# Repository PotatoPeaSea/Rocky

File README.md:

# Rocky — pentapod walker

Five-legged walking robot inspired by Rocky (Project Hail Mary).

- `fusion/` — Fusion 360 build scripts and BOM
- `pcb/` — integrated control PCB (KiCad): schematic, layout, STEP, fab outputs
- `sim/` — MuJoCo model and RL training environment
- `docs/` — design notes

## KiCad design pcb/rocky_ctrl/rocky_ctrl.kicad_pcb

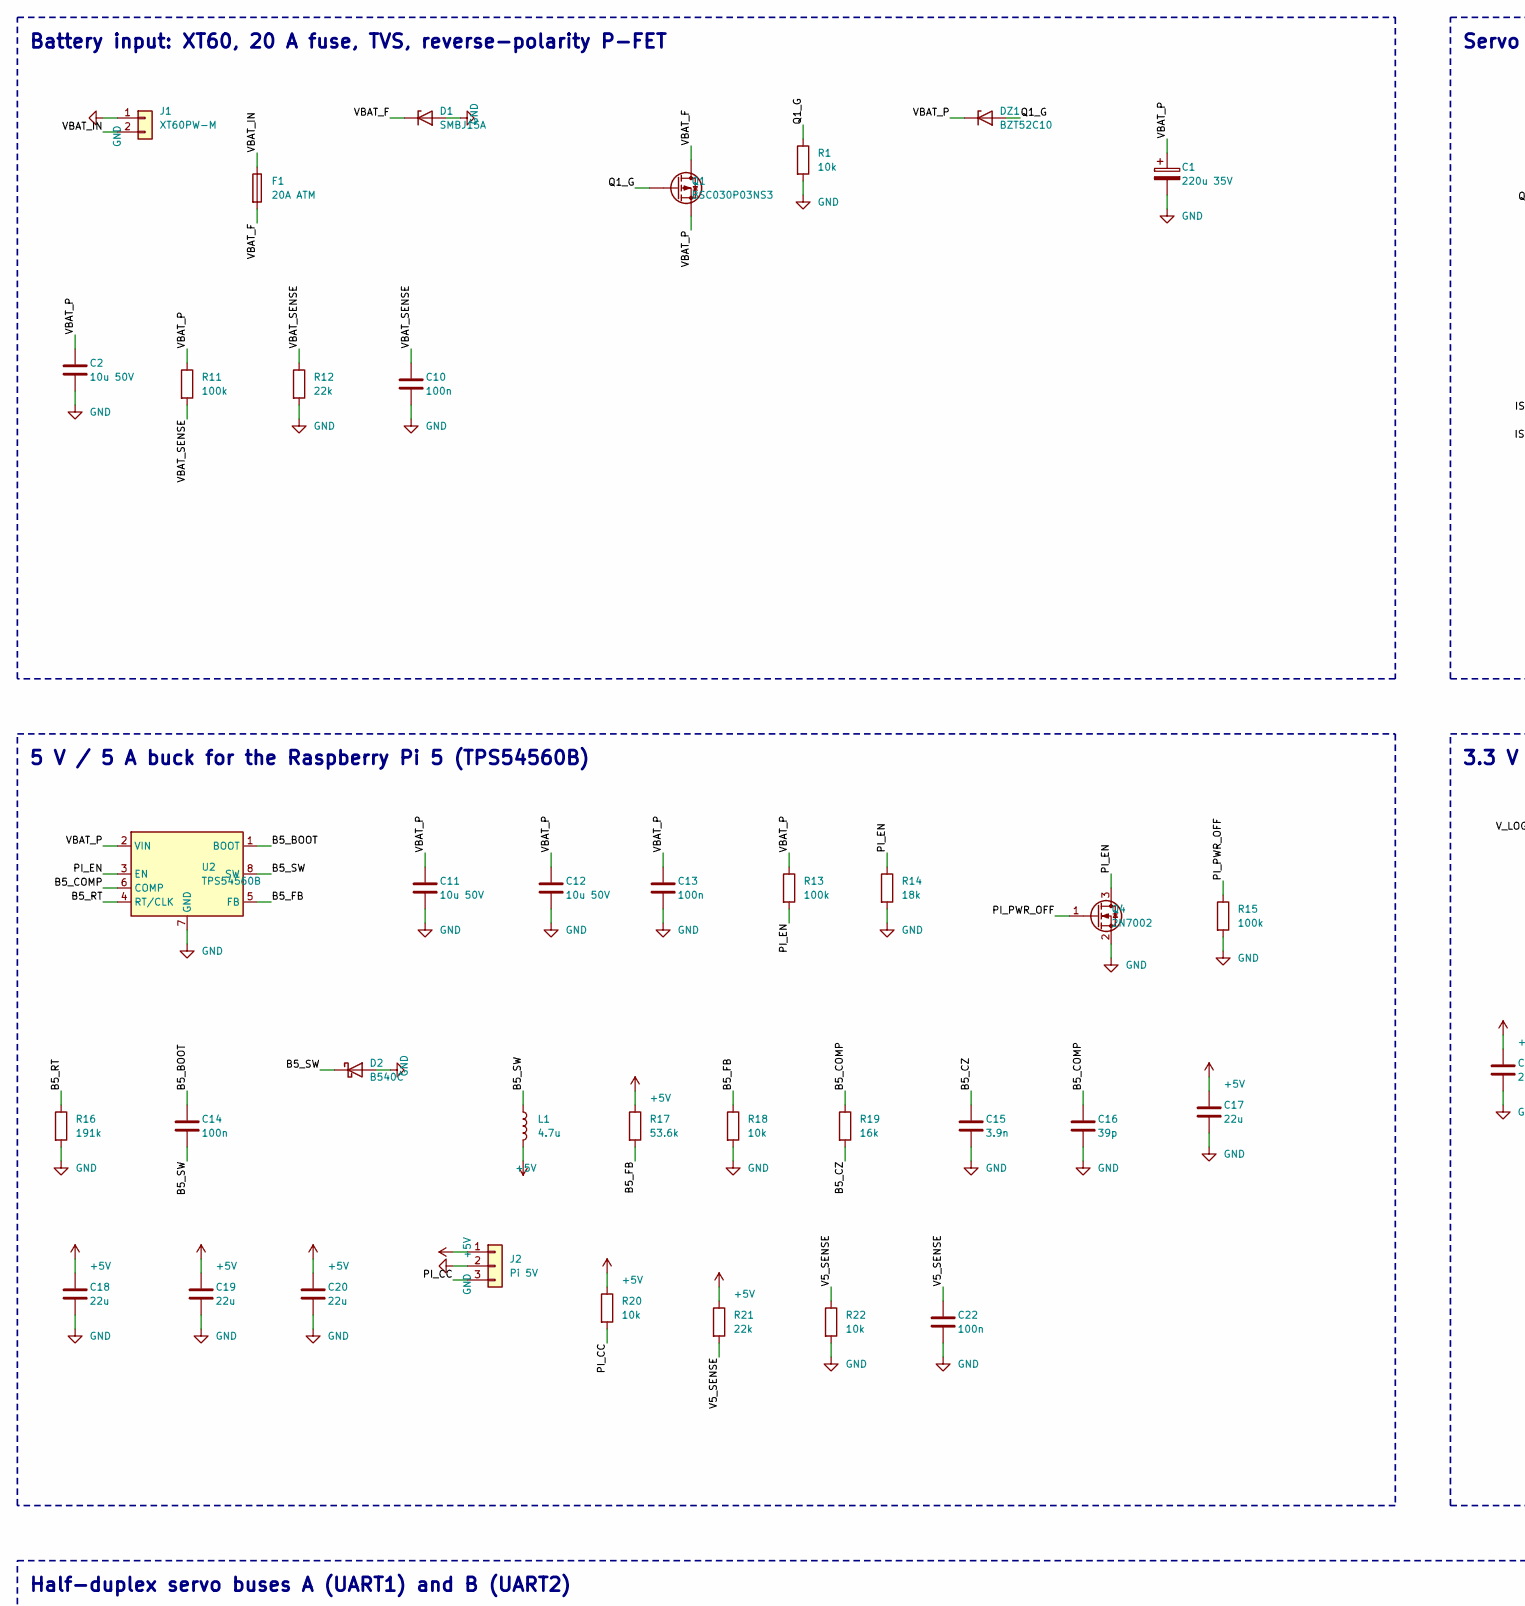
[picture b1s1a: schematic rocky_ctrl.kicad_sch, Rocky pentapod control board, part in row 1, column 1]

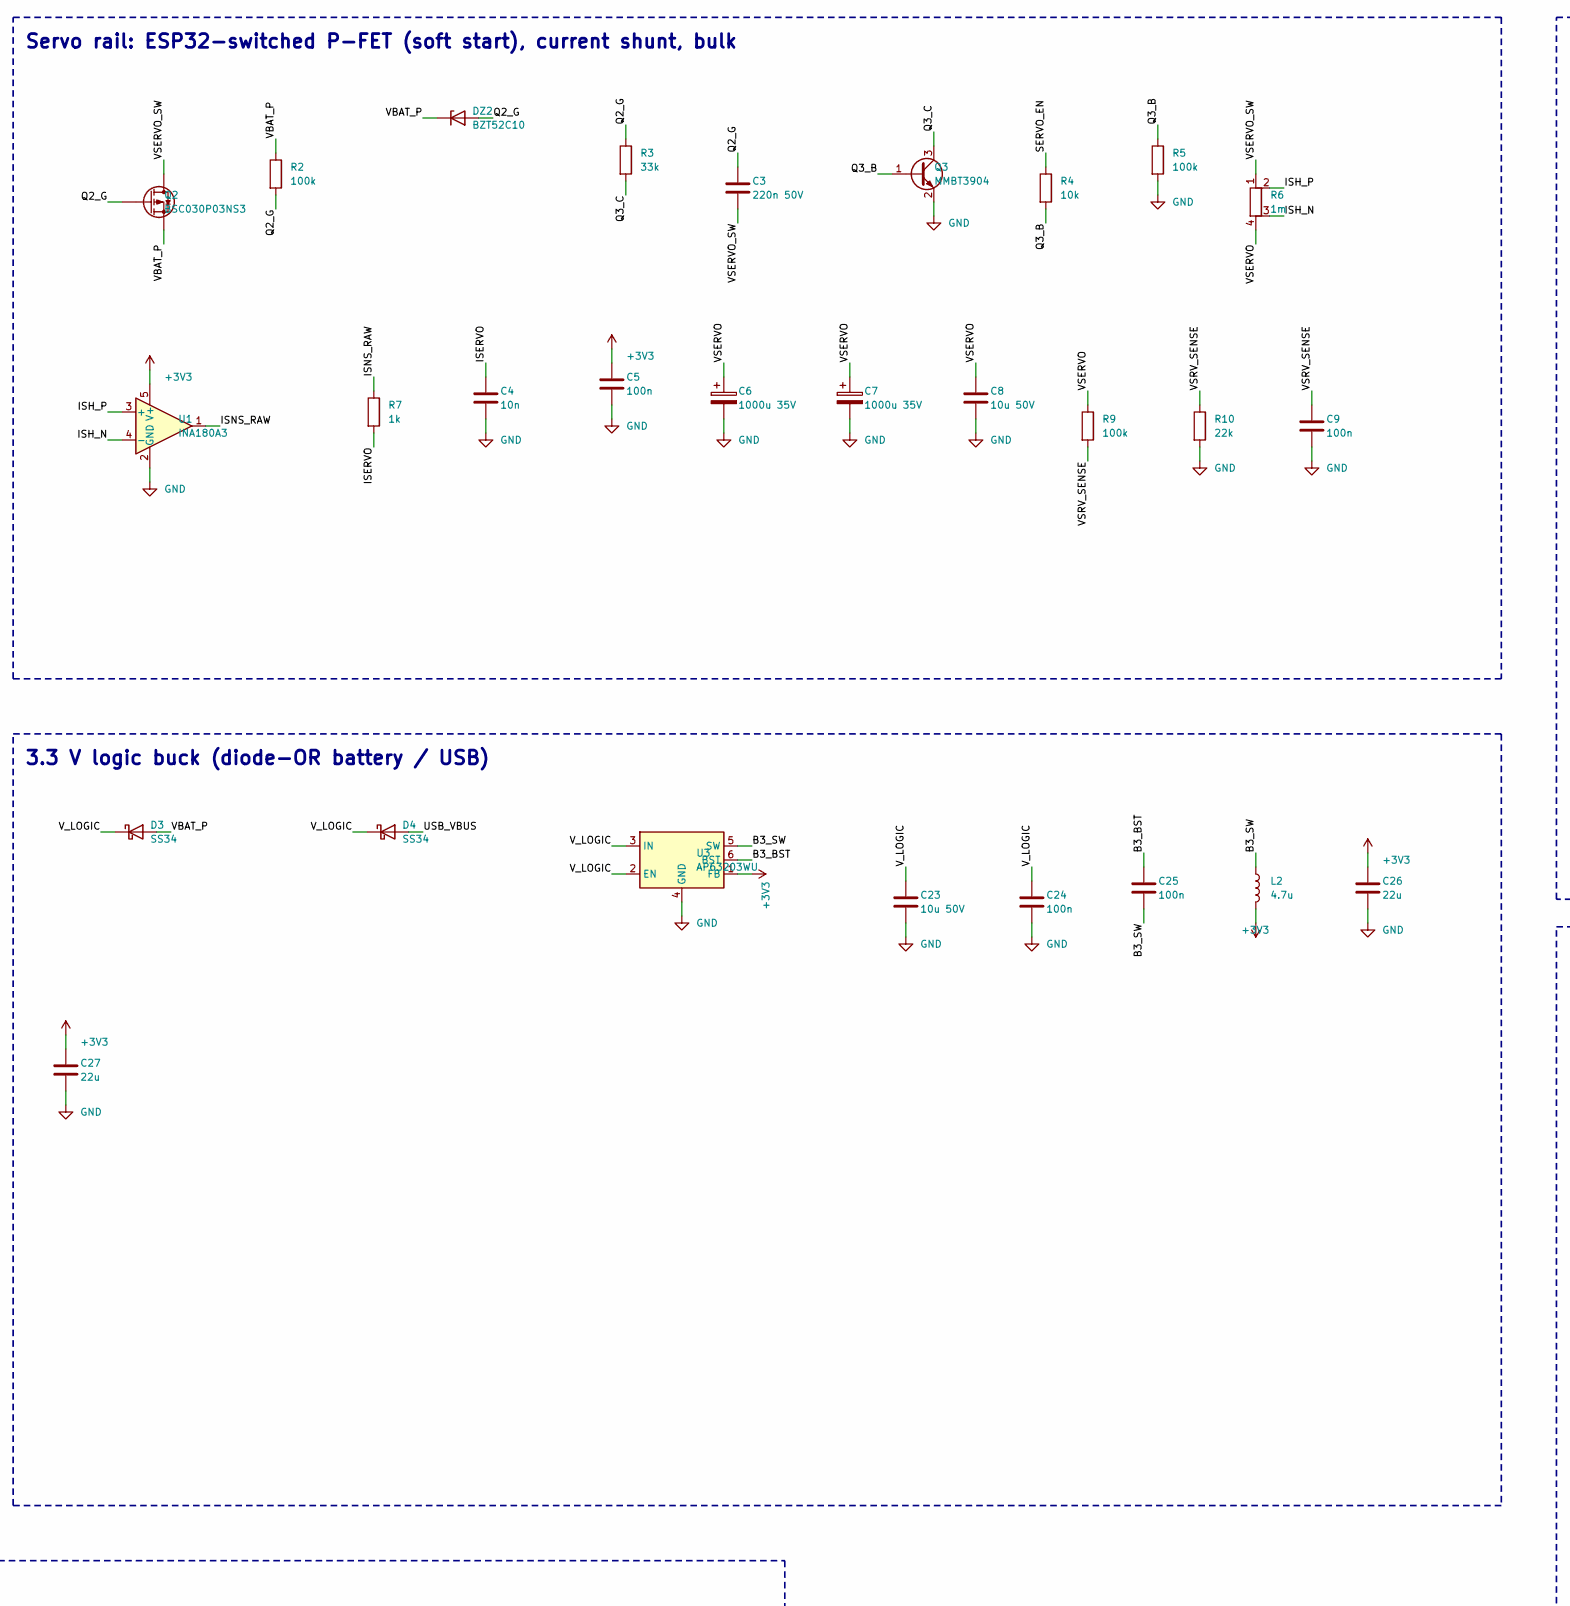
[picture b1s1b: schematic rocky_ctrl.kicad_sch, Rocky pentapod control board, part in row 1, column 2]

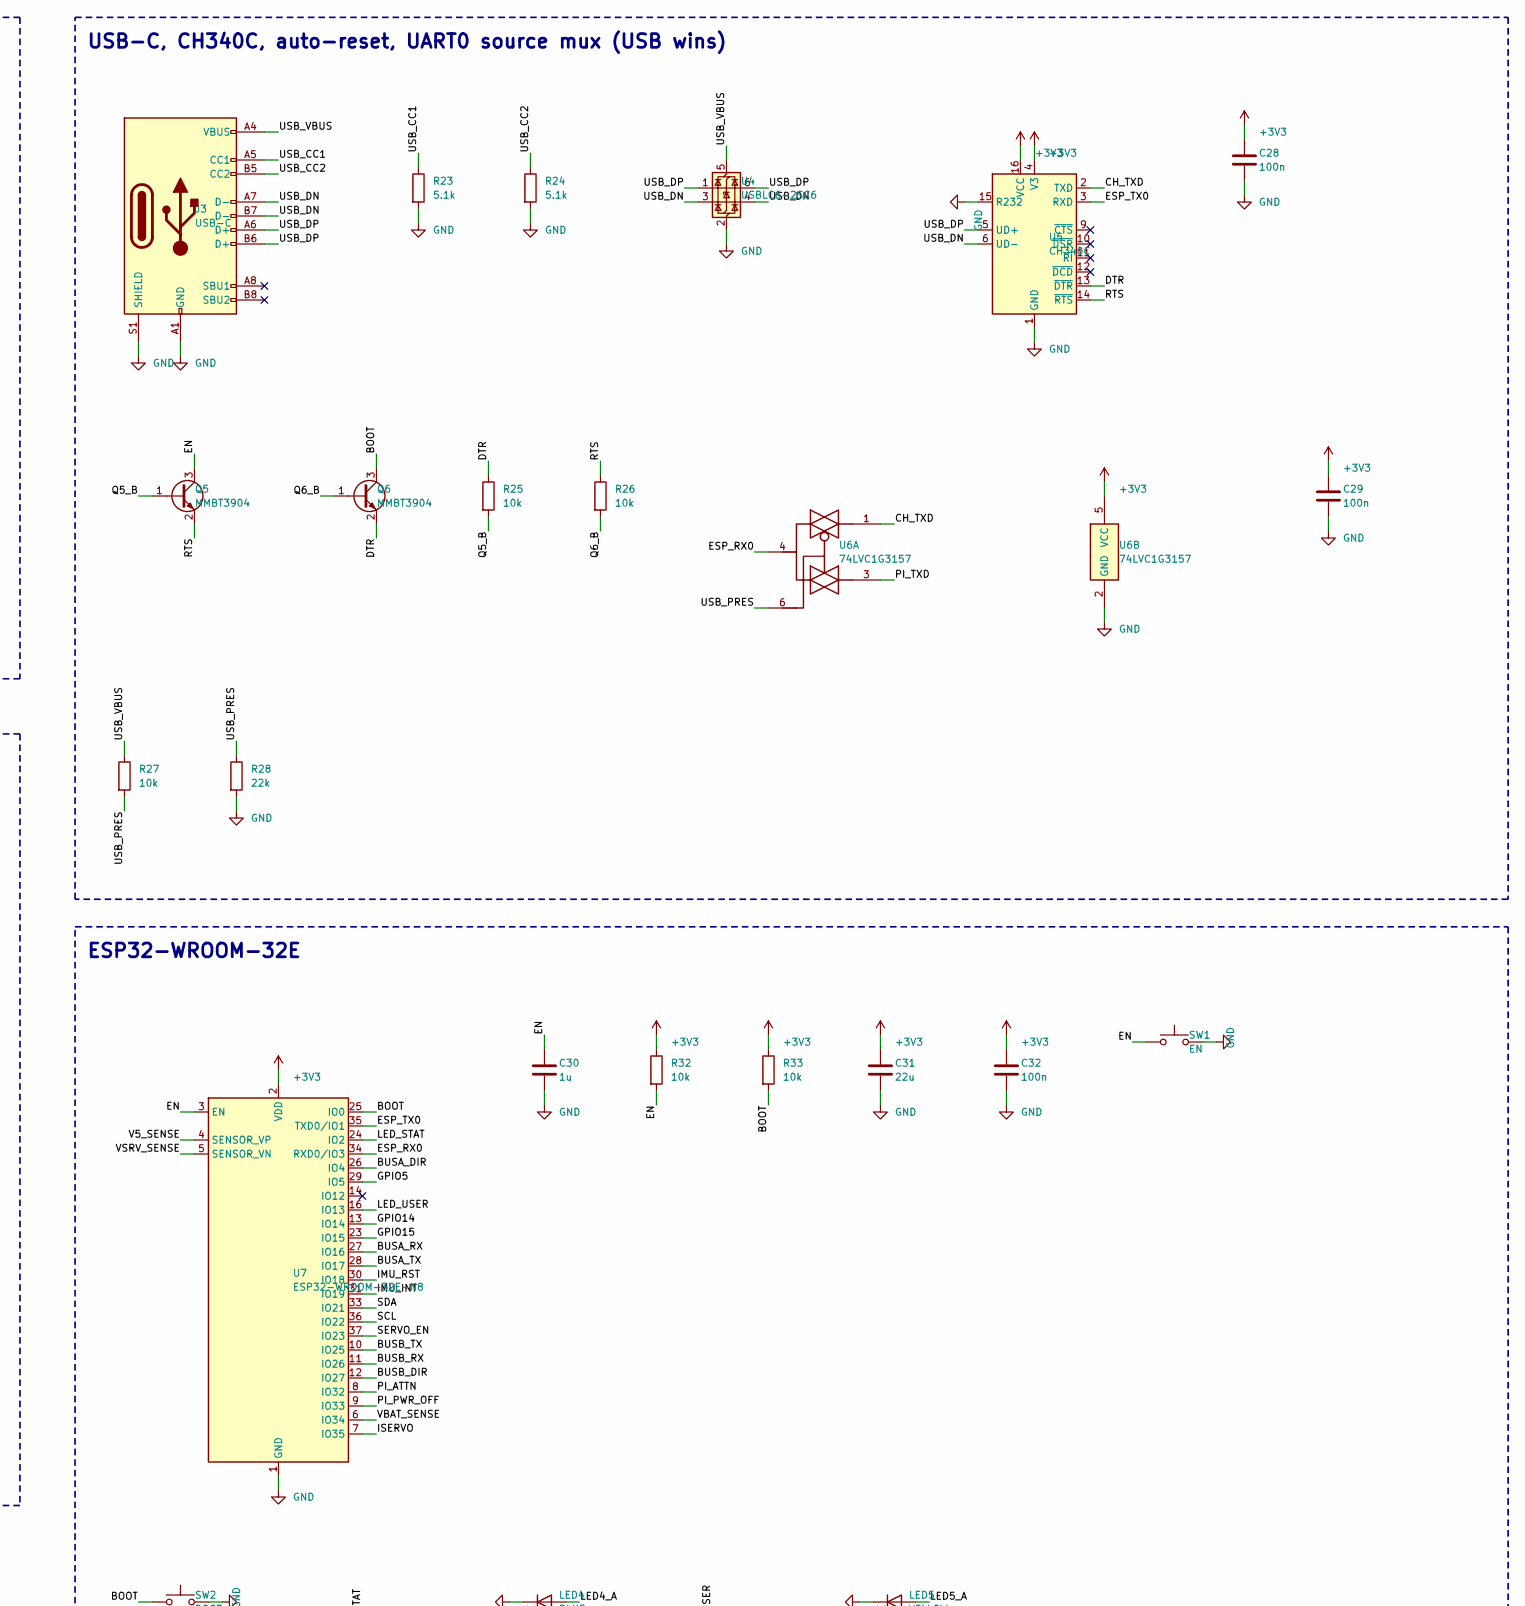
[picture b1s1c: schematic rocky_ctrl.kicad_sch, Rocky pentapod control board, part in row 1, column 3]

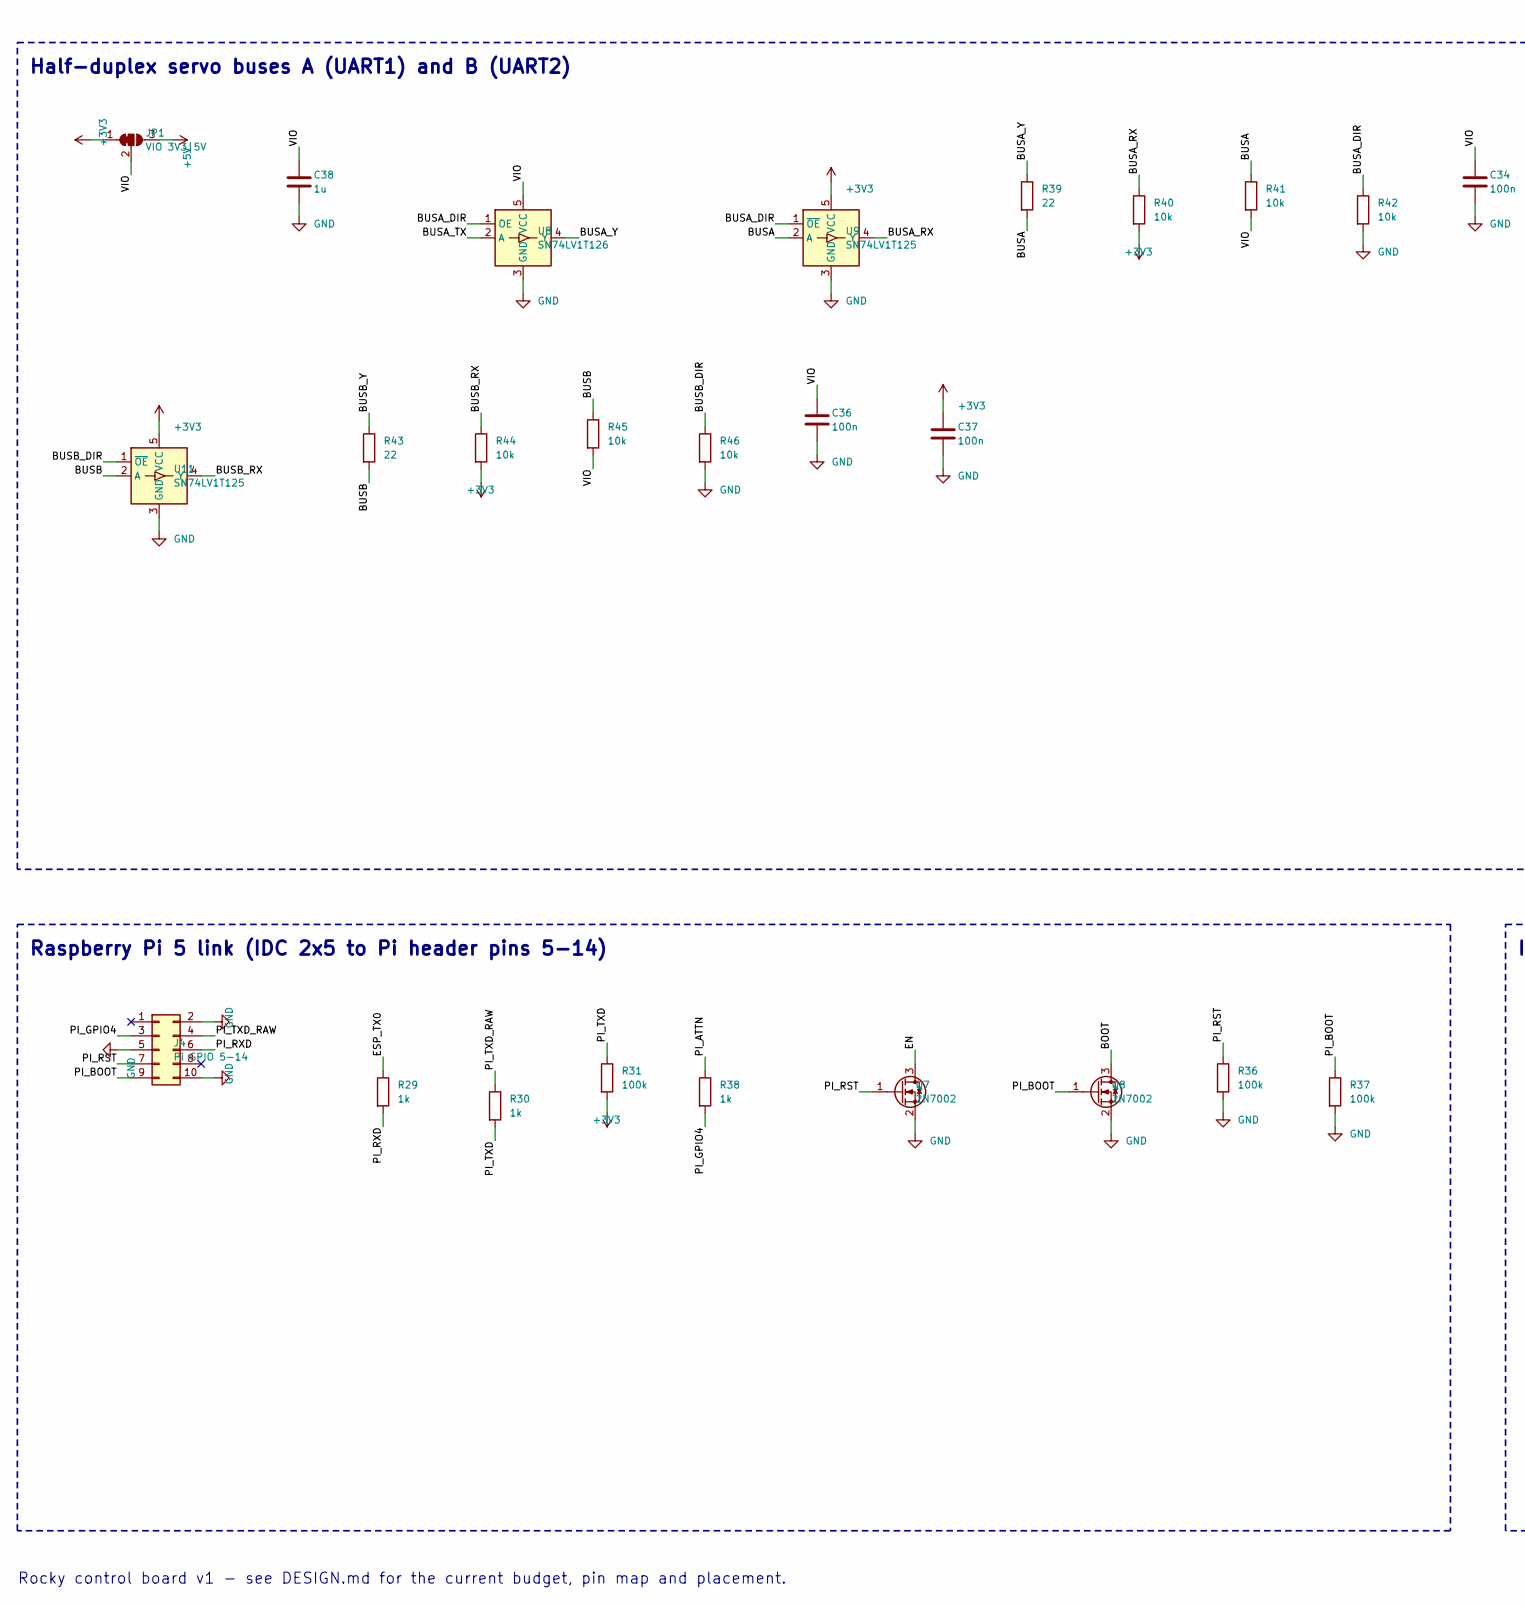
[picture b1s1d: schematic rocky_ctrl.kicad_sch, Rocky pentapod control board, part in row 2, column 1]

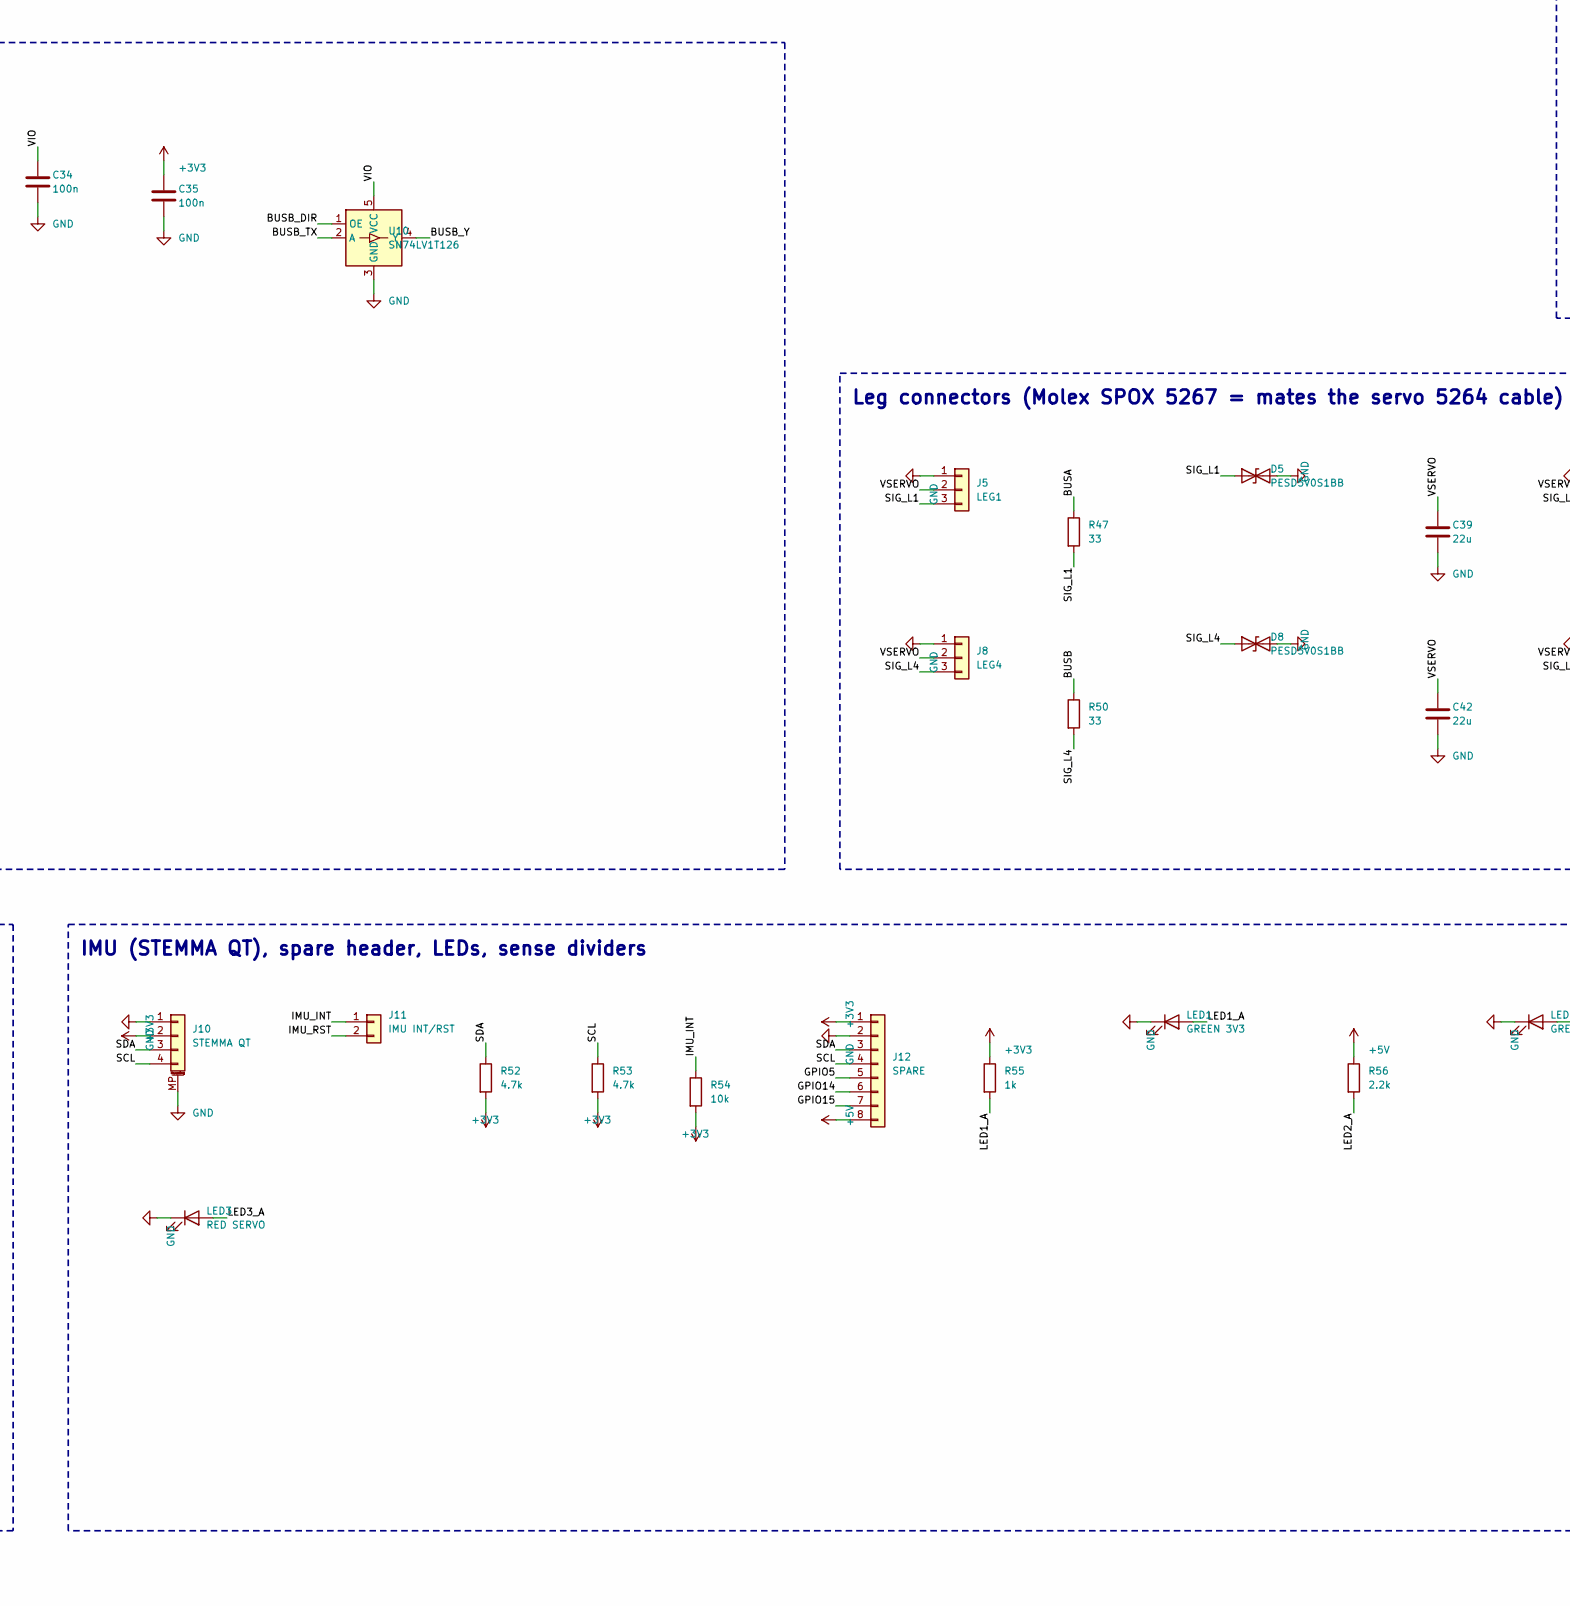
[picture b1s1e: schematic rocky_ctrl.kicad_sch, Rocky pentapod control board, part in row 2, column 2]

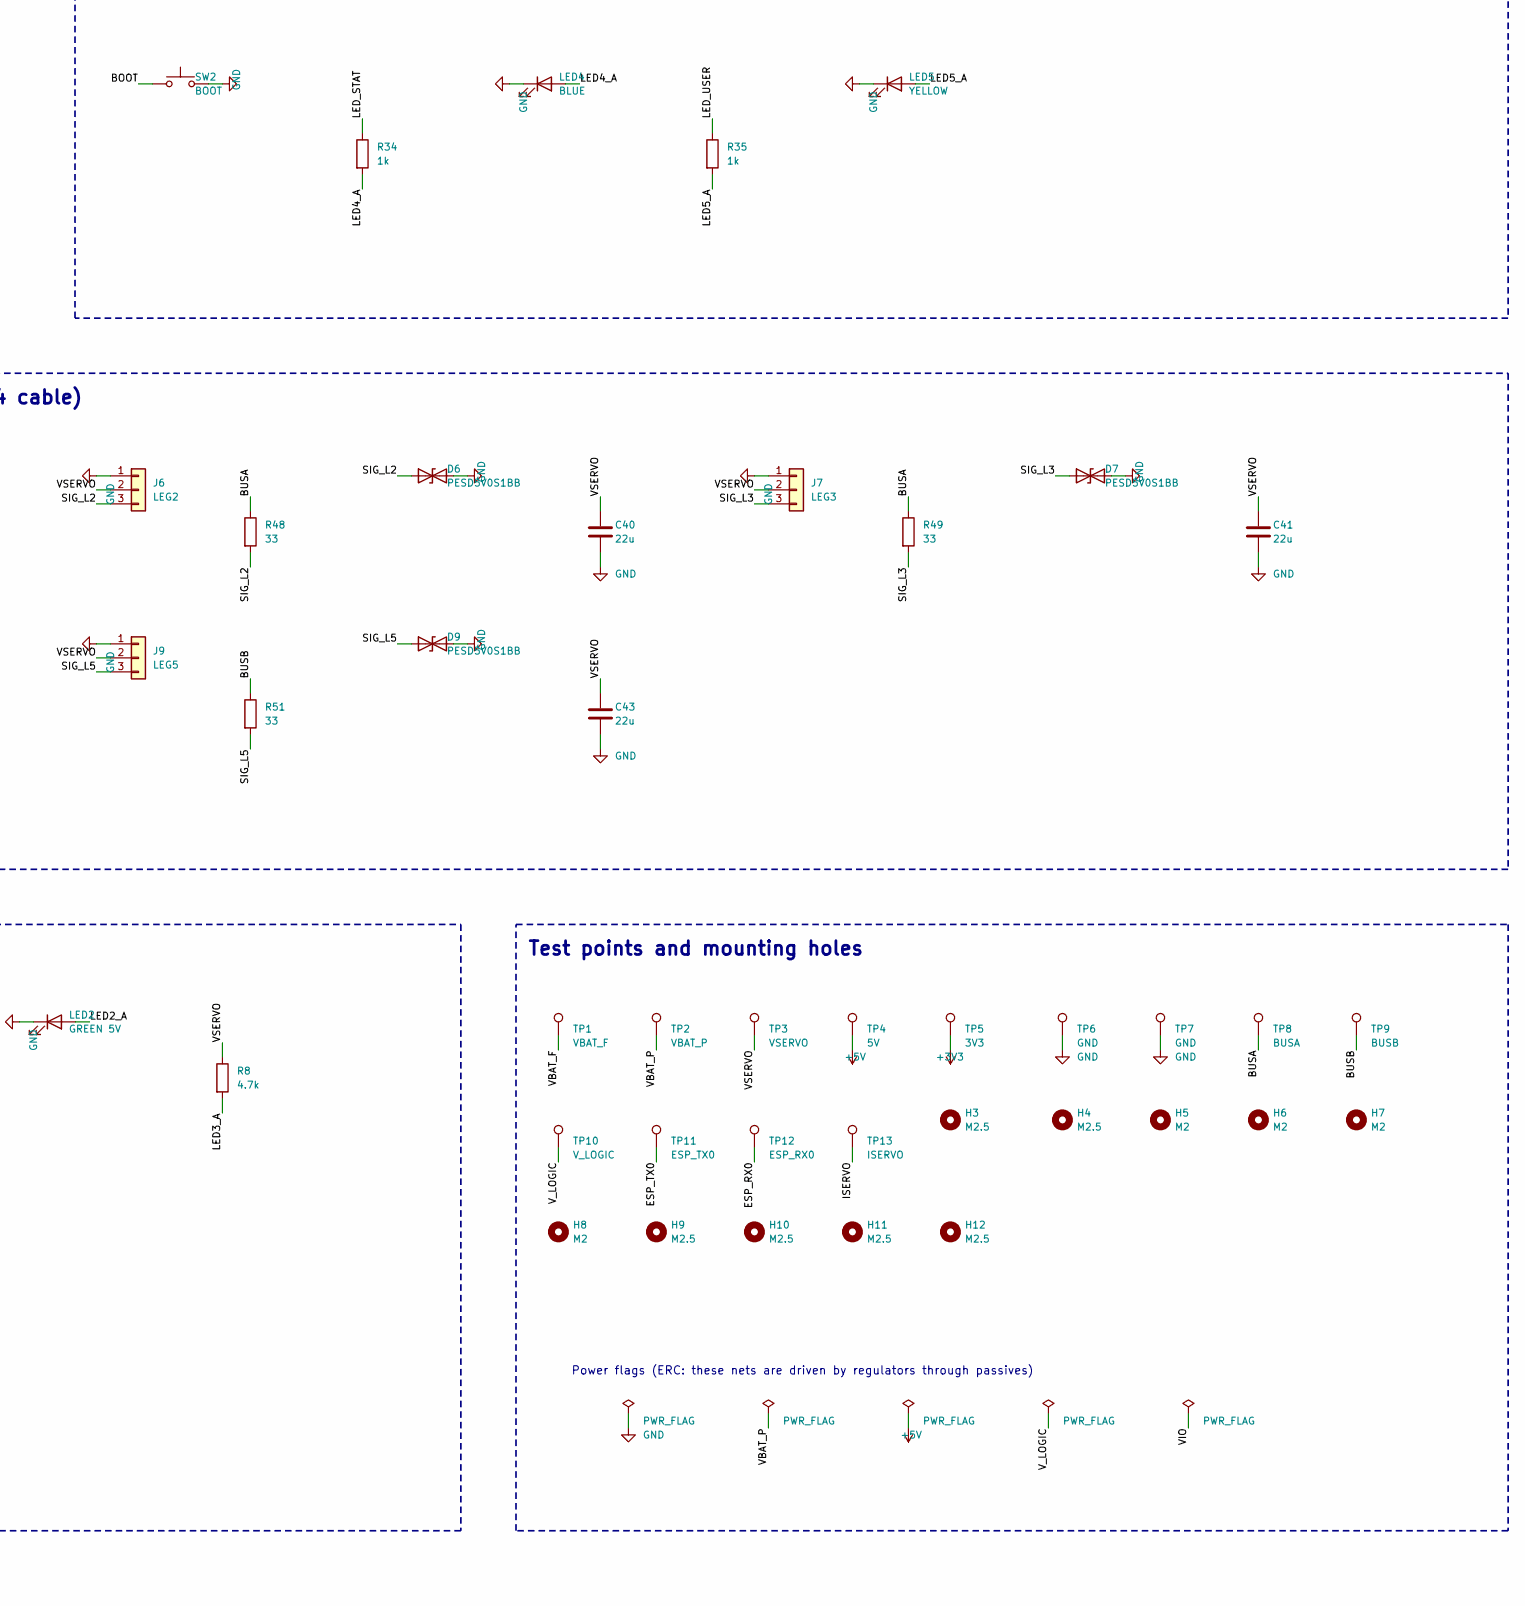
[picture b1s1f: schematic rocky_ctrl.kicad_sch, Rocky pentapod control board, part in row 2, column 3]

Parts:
C1: 220u 35V; CP_Radial_D8.0mm_P3.50mm; MPN Panasonic EEU-FR1V221 (220 uF 35 V, 8x1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
C2, C8, C11, C12, C23: 10u 50V; C_1206_3216Metric; MPN GRM31CR61H106KA12 (10 uF 50 V X5R 1206)
C3: 220n 50V; C_0805_2012Metric; MPN 220 nF 50 V X7R 0805 (Miller soft-start)
C4: 10n; C_0603_1608Metric; MPN 10n; LCSC C57112
C5, C9, C10, C13, C14, C22, C24, C25, C28, C29, C32, C34, C35, C36, C37: 100n; C_0603_1608Metric; MPN 100n; LCSC C14663
C6, C7: 1000u 35V; CP_Radial_D12.5mm_P5.00mm; MPN Panasonic EEU-FR1V102 (1000 uF 35 V, 12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
C15: 3.9n; C_0603_1608Metric; MPN 3.9n
C16: 39p; C_0603_1608Metric; MPN 39p
C17, C18, C19, C20, C26, C27, C31: 22u; C_0805_2012Metric; MPN 22 uF 25 V X5R 0805; LCSC C45783
C30, C38: 1u; C_0603_1608Metric; MPN 1u; LCSC C15849
C39, C40, C41, C42, C43: 22u; C_1206_3216Metric; MPN 22 uF 25 V X5R 1206
D1: SMBJ15A; D_SMB; MPN SMBJ15A (15 V stand-off unidirectional 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
D2: B540C; D_SMC; MPN B540C-13-F (40 V 5 A Schottky, SMC)
D3, D4: SS34; D_SMA; MPN SS34; LCSC C8678
D5, D6, D7, D8, D9: PESD5V0S1BB; D_SOD-323; MPN PESD5V0S1BB (bidirectional ESD, SOD-323)
DZ1, DZ2: BZT52C10; D_SOD-123; MPN BZT52C10 (10 V Vgs clamp)
F1: 20A ATM; Fuseholder_Blade_Mini_Keystone_3568; MPN Keystone 3568 + 20 A mini blade fuse
H3, H4, H9, H10, H11, H12: M2.5; MountingHole_2.7mm_M2.5; MPN M2.5 mounting hole
H5, H6, H7, H8: M2; MountingHole_2.2mm_M2; MPN M2 mounting hole
J1: XT60PW-M; AMASS_XT60PW-M_1x02_P7.20mm_Horizontal; MPN AMASS XT60PW-M
J2: Pi 5V; JST_VH_B3P-VH-B_1x03_P3.96mm_Vertical; MPN JST B3P-VH-B (to USB-C pigtail into the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
J3: USB-C; USB_C_Receptacle_HRO_TYPE-C-31-M-12; MPN HRO TYPE-C-31-M-12; LCSC C165948
J4: Pi GPIO 5-14; IDC-Header_2x05_P2.54mm_Vertical; MPN 2x5 2.54 mm box header (ribbon to Pi pi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
J5: LEG1; Molex_SPOX_5267-03A_1x03_P2.50mm_Vertical; MPN Molex 5267-03A (or 2.50 mm "5264" 3P ve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
J6: LEG2; Molex_SPOX_5267-03A_1x03_P2.50mm_Vertical; MPN Molex 5267-03A (or 2.50 mm "5264" 3P ve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
J7: LEG3; Molex_SPOX_5267-03A_1x03_P2.50mm_Vertical; MPN Molex 5267-03A (or 2.50 mm "5264" 3P ve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
J8: LEG4; Molex_SPOX_5267-03A_1x03_P2.50mm_Vertical; MPN Molex 5267-03A (or 2.50 mm "5264" 3P ve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
J9: LEG5; Molex_SPOX_5267-03A_1x03_P2.50mm_Vertical; MPN Molex 5267-03A (or 2.50 mm "5264" 3P ve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
J10: STEMMA QT; JST_SH_SM04B-SRSS-TB_1x04-1MP_P1.00mm_Horizontal; MPN JST SM04B-SRSS-TB (STEMMA QT to Adafrui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; LCSC C160390
J11: IMU INT/RST; PinHeader_1x02_P2.54mm_Vertical; MPN 1x2 2.54 mm header
J12: SPARE; PinHeader_1x08_P2.54mm_Vertical; MPN 1x8 2.54 mm header
JP1: VIO 3V3|5V; SolderJumper-3_P1.3mm_Bridged12_RoundedPad1.0x1.5mm; MPN solder jumper (default 3.3 V bus)
L1: 4.7u; L_Bourns_SRP1245A; MPN Bourns SRP1245A-4R7M (4.7 uH, Isat 21 A)
L2: 4.7u; L_Bourns_SRN6045TA; MPN Bourns SRN6045TA-4R7M (4.7 uH 3.4 A)
LED1: GREEN 3V3; LED_0603_1608Metric; MPN GREEN 3V3; LCSC C72043
LED2: GREEN 5V; LED_0603_1608Metric; MPN GREEN 5V; LCSC C72043
LED3: RED SERVO; LED_0603_1608Metric; MPN RED SERVO; LCSC C2286
LED4: BLUE; LED_0603_1608Metric; MPN BLUE; LCSC C72041
LED5: YELLOW; LED_0603_1608Metric; MPN YELLOW; LCSC C72038
Q1, Q2: BSC030P03NS3; TDSON-8-1; MPN Infineon BSC030P03NS3G (-30 V, 3.0 mOhm)
Q3, Q5, Q6: MMBT3904; SOT-23; MPN MMBT3904; LCSC C20526
Q4, Q7, Q8: 2N7002; SOT-23; MPN 2N7002; LCSC C8545
R1, R4, R18, R20, R22, R25, R26, R27, R32, R33, R40, R41, R42, R44, R45, R46, R54: 10k; R_0603_1608Metric; MPN 10k 1% 0603; LCSC C25804
R2, R5, R9, R11, R13, R15, R31, R36, R37: 100k; R_0603_1608Metric; MPN 100k 1% 0603; LCSC C25803
R3: 33k; R_0603_1608Metric; MPN 33k 1% 0603; LCSC C4216
R6: 1m; R_Shunt_Vishay_WSK2512_6332Metric_T1.19mm; MPN Vishay WSK25121L000FEA (1 mOhm 1 % 2512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
R7, R29, R30, R34, R35, R38, R55: 1k; R_0603_1608Metric; MPN 1k 1% 0603; LCSC C21190
R8, R52, R53: 4.7k; R_0603_1608Metric; MPN 4.7k 1% 0603; LCSC C23162
R10, R12, R21, R28: 22k; R_0603_1608Metric; MPN 22k 1% 0603; LCSC C31850
R14: 18k; R_0603_1608Metric; MPN 18k 1% 0603
R16: 191k; R_0603_1608Metric; MPN 191k 1% 0603
R17: 53.6k; R_0603_1608Metric; MPN 53.6k 1% 0603
R19: 16k; R_0603_1608Metric; MPN 16k 1% 0603
R23, R24: 5.1k; R_0603_1608Metric; MPN 5.1k 1% 0603; LCSC C23186
R39, R43: 22; R_0603_1608Metric; MPN 22 1% 0603; LCSC C23345
R47, R48, R49, R50, R51: 33; R_0603_1608Metric; MPN 33 1% 0603; LCSC C23140
R56: 2.2k; R_0603_1608Metric; MPN 2.2k 1% 0603; LCSC C4190
SW1: EN; SW_Push_1P1T_XKB_TS-1187A; MPN XKB TS-1187A-B-A-B; LCSC C318884
SW2: BOOT; SW_Push_1P1T_XKB_TS-1187A; MPN XKB TS-1187A-B-A-B; LCSC C318884
TP1: VBAT_F; TestPoint_Pad_D1.5mm; MPN test pad 1.5 mm
TP2: VBAT_P; TestPoint_Pad_D1.5mm; MPN test pad 1.5 mm
TP3: VSERVO; TestPoint_Pad_D1.5mm; MPN test pad 1.5 mm
TP4: 5V; TestPoint_Pad_D1.5mm; MPN test pad 1.5 mm
TP5: 3V3; TestPoint_Pad_D1.5mm; MPN test pad 1.5 mm
TP6, TP7: GND; TestPoint_Pad_D1.5mm; MPN test pad 1.5 mm
TP8: BUSA; TestPoint_Pad_D1.5mm; MPN test pad 1.5 mm
TP9: BUSB; TestPoint_Pad_D1.5mm; MPN test pad 1.5 mm
TP10: V_LOGIC; TestPoint_Pad_D1.5mm; MPN test pad 1.5 mm
TP11: ESP_TX0; TestPoint_Pad_D1.5mm; MPN test pad 1.5 mm
TP12: ESP_RX0; TestPoint_Pad_D1.5mm; MPN test pad 1.5 mm
TP13: ISERVO; TestPoint_Pad_D1.5mm; MPN test pad 1.5 mm
U1: INA180A3; SOT-23-5; MPN INA180A3IDBVR (100 V/V)
U2: TPS54560B; Texas_R-PDSO-G8_EP2.95x4.9mm_Mask2.4x3.1mm_ThermalVias; MPN TPS54560BDDAR
U3: AP63203WU; TSOT-23-6; MPN AP63203WU-7
U4: USBLC6-2SC6; SOT-23-6; MPN USBLC6-2SC6; LCSC C7519
U5: CH340C; SOIC-16_3.9x9.9mm_P1.27mm; MPN CH340C; LCSC C84681
U6: 74LVC1G3157; SOT-363_SC-70-6; MPN SN74LVC1G3157DCKR (S=L: B1=Pi, S=H: B2=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
U7: ESP32-WROOM-32E-N8; ESP32-WROOM-32E; MPN ESP32-WROOM-32E-N8 (8 MB); LCSC C701342
U8, U10: SN74LV1T126; SOT-23-5; MPN SN74LV1T126DBVR (TX driver, OE high)
U9, U11: SN74LV1T125; SOT-23-5; MPN SN74LV1T125DBVR (RX buffer, OE low)

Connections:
+3V3: C5.1, C26.1, C27.1, C28.1, C29.1, C31.1, C32.1, C35.1, C37.1, J10.2, J12.1, JP1.1 (A), L2.2, R31.2, R32.1, R33.1, R40.2, R44.2, R52.2, R53.2, R54.2, R55.1, TP5.1, U1.5 (V+), U3.1 (FB), U5.4 (V3), U5.16 (VCC), U6.5 (VCC), U7.2 (VDD), U9.5 (VCC), U11.5 (VCC)
+5V: C17.1, C18.1, C19.1, C20.1, J2.1, J12.8, JP1.3 (B), L1.2, R17.1, R20.1, R21.1, R56.1, TP4.1
/B3_BST: C25.1, U3.6 (BST)
/B3_SW: C25.2, L2.1, U3.5 (SW)
/B5_BOOT: C14.1, U2.1 (BOOT)
/B5_COMP: C16.1, R19.1, U2.6 (COMP)
/B5_CZ: C15.1, R19.2
/B5_FB: R17.2, R18.1, U2.5 (FB)
/B5_RT: R16.1, U2.4 (RT/CLK)
/B5_SW: C14.2, D2.1 (K), L1.1, U2.8 (SW)
/BOOT: Q6.3 (C), Q8.3 (D), R33.2, SW2.1, U7.25 (IO0)
/BUSA: R39.2, R41.1, R47.1, R48.1, R49.1, TP8.1, U9.2 (A)
/BUSA_DIR: R42.1, U7.26 (IO4), U8.1 (OE), U9.1 (~OE)
/BUSA_RX: R40.1, U7.27 (IO16), U9.4 (Y)
/BUSA_TX: U7.28 (IO17), U8.2 (A)
/BUSA_Y: R39.1, U8.4 (Y)
/BUSB: R43.2, R45.1, R50.1, R51.1, TP9.1, U11.2 (A)
/BUSB_DIR: R46.1, U7.12 (IO27), U10.1 (OE), U11.1 (~OE)
/BUSB_RX: R44.1, U7.11 (IO26), U11.4 (Y)
/BUSB_TX: U7.10 (IO25), U10.2 (A)
/BUSB_Y: R43.1, U10.4 (Y)
/CH_TXD: U5.2 (TXD), U6.1
/DTR: Q6.2 (E), R25.1, U5.13 (~DTR)
/EN: C30.1, Q5.3 (C), Q7.3 (D), R32.2, SW1.1, U7.3 (EN)
/ESP_RX0: TP12.1, U6.4, U7.34 (RXD0/IO3)
/ESP_TX0: R29.1, TP11.1, U5.3 (RXD), U7.35 (TXD0/IO1)
/GPIO5: J12.5, U7.29 (IO5)
/GPIO14: J12.6, U7.13 (IO14)
/GPIO15: J12.7, U7.23 (IO15)
/IMU_INT: J11.1, R54.1, U7.31 (IO19)
/IMU_RST: J11.2, U7.30 (IO18)
/ISERVO: C4.1, R7.2, TP13.1, U7.7 (IO35)
/ISH_N: R6.3, U1.4 (-)
/ISH_P: R6.2, U1.3 (+)
/ISNS_RAW: R7.1, U1.1
/LED1_A: LED1.2 (A), R55.2
/LED2_A: LED2.2 (A), R56.2
/LED3_A: LED3.2 (A), R8.2
/LED4_A: LED4.2 (A), R34.2
/LED5_A: LED5.2 (A), R35.2
/LED_STAT: R34.1, U7.24 (IO2)
/LED_USER: R35.1, U7.16 (IO13)
/PI_ATTN: R38.1, U7.8 (IO32)
/PI_BOOT: J4.9, Q8.1 (G), R37.1
/PI_CC: J2.3, R20.2
/PI_EN: Q4.3 (D), R13.2, R14.1, U2.3 (EN)
/PI_GPIO4: J4.3, R38.2
/PI_PWR_OFF: Q4.1 (G), R15.1, U7.9 (IO33)
/PI_RST: J4.7, Q7.1 (G), R36.1
/PI_RXD: J4.6, R29.2
/PI_TXD: R30.2, R31.1, U6.3
/PI_TXD_RAW: J4.4, R30.1
/Q1_G: DZ1.2 (A), Q1.4 (G), R1.1
/Q2_G: C3.1, DZ2.2 (A), Q2.4 (G), R2.2, R3.1
/Q3_B: Q3.1 (B), R4.2, R5.1
/Q3_C: Q3.3 (C), R3.2
/Q5_B: Q5.1 (B), R25.2
/Q6_B: Q6.1 (B), R26.2
/RTS: Q5.2 (E), R26.1, U5.14 (~RTS)
/SCL: J10.4, J12.4, R53.1, U7.36 (IO22)
/SDA: J10.3, J12.3, R52.1, U7.33 (IO21)
/SERVO_EN: R4.1, U7.37 (IO23)
/SIG_L1: D5.1 (A1), J5.3, R47.2
/SIG_L2: D6.1 (A1), J6.3, R48.2
/SIG_L3: D7.1 (A1), J7.3, R49.2
/SIG_L4: D8.1 (A1), J8.3, R50.2
/SIG_L5: D9.1 (A1), J9.3, R51.2
/USB_CC1: J3.A5 (CC1), R23.1
/USB_CC2: J3.B5 (CC2), R24.1
/USB_DN: J3.A7 (D-), J3.B7 (D-), U4.3 (I/O2), U4.4 (I/O2), U5.6 (UD-)
/USB_DP: J3.A6 (D+), J3.B6 (D+), U4.1 (I/O1), U4.6 (I/O1), U5.5 (UD+)
/USB_PRES: R27.2, R28.1, U6.6
/USB_VBUS: D4.2 (A), J3.A4 (VBUS), J3.A9 (VBUS), J3.B4 (VBUS), J3.B9 (VBUS), R27.1, U4.5 (VBUS)
/V5_SENSE: C22.1, R21.2, R22.1, U7.4 (SENSOR_VP)
/VBAT_F: D1.1 (K), F1.2, Q1.5 (D), TP1.1
/VBAT_IN: F1.1, J1.2
/VBAT_P: C1.1, C2.1, C11.1, C12.1, C13.1, D3.2 (A), DZ1.1 (K), DZ2.1 (K), Q1.1 (S), Q1.2 (S), Q1.3 (S), Q2.1 (S), Q2.2 (S), Q2.3 (S), R2.1, R11.1, R13.1, TP2.1, U2.2 (VIN)
/VBAT_SENSE: C10.1, R11.2, R12.1, U7.6 (IO34)
/VIO: C34.1, C36.1, C38.1, JP1.2 (C), R41.2, R45.2, U8.5 (VCC), U10.5 (VCC)
/VSERVO: C6.1, C7.1, C8.1, C39.1, C40.1, C41.1, C42.1, C43.1, J5.2, J6.2, J7.2, J8.2, J9.2, R6.4, R8.1, R9.1, TP3.1
/VSERVO_SW: C3.2, Q2.5 (D), R6.1
/VSRV_SENSE: C9.1, R9.2, R10.1, U7.5 (SENSOR_VN)
/V_LOGIC: C23.1, C24.1, D3.1 (K), D4.1 (K), TP10.1, U3.2 (EN), U3.3 (IN)
GND: C1.2, C2.2, C4.2, C5.2, C6.2, C7.2, C8.2, C9.2, C10.2, C11.2, C12.2, C13.2, C15.2, C16.2, C17.2, C18.2, C19.2, C20.2, C22.2, C23.2, C24.2, C26.2, C27.2, C28.2, C29.2, C30.2, C31.2, C32.2, C34.2, C35.2, C36.2, C37.2, C38.2, C39.2, C40.2, C41.2, C42.2, C43.2, D1.2 (A), D2.2 (A), D5.2 (A2), D6.2 (A2), D7.2 (A2), D8.2 (A2), D9.2 (A2), J1.1, J2.2, J3.A1 (GND), J3.A12 (GND), J3.B1 (GND), J3.B12 (GND), J3.S1 (SHIELD), J4.2, J4.5, J4.10, J5.1, J6.1, J7.1, J8.1, J9.1, J10.1, J10.MP (MountPin), J12.2, LED1.1 (K), LED2.1 (K), LED3.1 (K), LED4.1 (K), LED5.1 (K), Q3.2 (E), Q4.2 (S), Q7.2 (S), Q8.2 (S), R1.2, R5.2, R10.2, R12.2, R14.2, R15.2, R16.2, R18.2, R22.2, R23.2, R24.2, R28.2, R36.2, R37.2, R42.2, R46.2, SW1.2, SW2.2, TP6.1, TP7.1, U1.2 (GND), U2.7 (GND), U2.9 (GND), U3.4 (GND), U4.2 (GND), U5.1 (GND), U5.15 (R232), U6.2 (GND), U7.1 (GND), U7.15 (GND), U7.38 (GND), U7.39 (GND), U8.3 (GND), U9.3 (GND), U10.3 (GND), U11.3 (GND)

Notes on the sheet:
Battery input: XT60, 20 A fuse, TVS, reverse-polarity P-FET
Servo rail: ESP32-switched P-FET (soft start), current shunt, bulk
5 V / 5 A buck for the Raspberry Pi 5 (TPS54560B)
3.3 V logic buck (diode-OR battery / USB)
USB-C, CH340C, auto-reset, UART0 source mux (USB wins)
ESP32-WROOM-32E
Half-duplex servo buses A (UART1) and B (UART2)
Leg connectors (Molex SPOX 5267 = mates the servo 5264 cable)
Raspberry Pi 5 link (IDC 2x5 to Pi header pins 5-14)
IMU (STEMMA QT), spare header, LEDs, sense dividers
Test points and mounting holes
Power flags (ERC: these nets are driven by regulators through passives)
Rocky control board v1 - see DESIGN.md for the current budget, pin map and placement.
